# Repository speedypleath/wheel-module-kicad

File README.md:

# Haptic Console - Wheel Module (M3) Encoder Sensor Board

KiCad project for the electronics of the Wheel Module (M3) of Haptic Console v1.0,
part of the ITPMA dissertation *Tactile I/O: Exploring physicality in MIDI controllers*.

The mechanical side of this module (200 mm DIN aluminium handwheel, PETG shaft,
6204-2RS bearings, GT2 1:1 belt drive) is documented in the Obsidian vault under
`Notes/Haptic Console - Handwheel Belt Drive Module Plan.md`. This repository covers
only the sensor board that reads the optical encoder and presents it to the console.

## What the board does

The handwheel drives an E38S6G5-600B-G24N 600 P/R optical encoder through a 1:1 GT2
belt. A Raspberry Pi Pico reads the A/B quadrature signals locally, converts them into a clean position
packet, and exposes that packet to the Teensy 4.1 master over I2C. The module behaves
as a self-contained tactile sense organ rather than a peer processor, matching the
connector standard's design philosophy.

*The module as actually built. Component side, left to right: `J2` (black 5-pin encoder
header) and the pull-up/series resistors bottom left, `C2` (yellow disc) beside them,
`U1` centre with `C1`'s electrolytic can at its USB end, `J1` (white XH2.54 to the hub)
top right, and the `D1`/`D2` status LEDs bottom right.*

## The encoder interface, and why the pull-ups are there

The encoder is an **E38S6G5-600B-G24N**: photoelectric incremental, 600 P/R, rated
**DC 5-24V**, with **NPN open-collector** outputs. The `600B` suffix denotes **AB
two-phase — there is no Z index channel**. Absolute zero is established in firmware,
not from hardware index.

The open-collector output is the important electrical detail. An open-collector output can
only pull its line *low*. It never drives a line high. The high level is therefore set
entirely by whatever rail the line is pulled up to, and is completely independent of
the encoder's own supply voltage.

That gives the safety property this board relies on:

- `R1`, `R2` (4.7k) pull `ENC_A_RAW` and `ENC_B_RAW` up to **+3V3**.
- The Pico therefore sees a 0V to 3.3V swing regardless of whether the encoder is run
  from 5V or 12V.
- `R4`, `R5` (330R) sit in series into the Pico GPIO as fault-current limiters,
  protecting the pin if a line is ever accidentally shorted to the encoder supply.

4.7k is comfortable here. With ~2 m of encoder cable at roughly 120 pF/m plus pin and
stray capacitance (~300 pF total), the RC rise time is about 3 us 10-90%. At a realistic
handwheel speed of 300 rev/min each channel runs at 3 kHz, a 333 us period, so the rise
occupies under 1% of it. Pull-up current is 0.7 mA per line, far inside the output
stage's sink capability.

Without the pull-ups the inputs would float and the quadrature decode would be noise.
The pull-ups are not optional here.

Encoder power is taken from the console's **5V rail**, which is inside the encoder's
rated 5-24V window. If the encoder proves sluggish or noisy at 5V, the documented
alternative is a small 5V to 12V boost feeding `J2` pin 1 only. Because the pull-ups
reference 3.3V, that change requires **no** modification to the logic side.

**Decision, 2026-08-28: the 12V path is deliberately not built.** The planned Eurorack
translation module needs 24V regardless, so if a higher-voltage rail is ever added it
should be designed once for both modules rather than bolted onto M3 alone. Treat 5V as
the committed supply until that point. Note also that if the encoder signals ever look
sluggish, supply voltage is the *less* likely cause: edge shape here is set by the
pull-up RC (4.7k against ~300 pF, ~3 us) which does not change with encoder supply at
all. Rounded edges point at the pull-ups (fit 2.2k or 1k); missed counts that worsen
with rotation speed point at the supply.

## Console interface

`J1` is the standard **XH2.54 6-pin** inter-module connector (standard v1.1):

| Pin | Signal | Board use |
|---|---|---|
| 1 | GND | Common ground |
| 2 | 3.3V | **Not connected** (see below) |
| 3 | 5V | Powers the Pico via VSYS, and the encoder |
| 4 | SIG1 / SDA | I2C data, Pico GP4 |
| 5 | SIG2 / SCL | I2C clock, Pico GP5 |
| 6 | SIG3 / IRQ | Data-ready, Pico GP6 |

Pin 2 is deliberately left unconnected. The connector standard warns against feeding
both VSYS and 3V3 as competing power paths into a Pico. The board takes 5V into VSYS
and uses the Pico's own regulated 3V3 output as the logic reference for the pull-ups.

I2C bus pull-ups live on the master/hub board, not here, per the same standard.

## Encoder connector

`J2` is a 5-pin 2.54mm header matching the encoder's four conductors plus its shield:

| Pin | Encoder wire | Board use |
|---|---|---|
| 1 | Red | V+, from the console 5V rail |
| 2 | Black | 0V / GND |
| 3 | White | Channel A, to `R1`/`R4` |
| 4 | Green | Channel B, to `R2`/`R5` |
| 5 | Bare / foil | Cable shield, to GND |

Pin 5 carried `ENC_Z` in the first revision. The encoder has no Z channel, so it is now
the shield return, terminated to GND **at the board end only** — single-point, to avoid
a ground loop down the 2 m cable run.

## Pin map

| Pico pin | Net | Function |
|---|---|---|
| GP2 (pin 4) | LNK | Link/comms status LED |
| GP4 (pin 6) | SDA | I2C target data |
| GP5 (pin 7) | SCL | I2C target clock |
| GP6 (pin 9) | IRQ | Data-ready out to master |
| GP16 (pin 21) | ENC_A | Encoder channel A |
| GP17 (pin 22) | ENC_B | Encoder channel B |
| VSYS (pin 39) | +5V | Module power in |
| 3V3 (pin 36) | +3V3 | Logic reference out |

At 600 P/R with 4x quadrature decoding, one full handwheel turn is 2400 counts.

## Why C1 is there, and why it is an electrolytic

C1 is a **bulk reservoir**, not a decoupling capacitor, and the two jobs are
different. C2 (100 nF on 3V3) is decoupling: it kills the nanosecond-scale current
spikes from GPIO switching, and wants to be small and close to the pin. C1 sits on
the 5 V rail at the connector entry and does the opposite job — it is a local charge
store at the far end of the hub cable.

The 5 V arrives over a metre or two of XH2.54 flying lead, perhaps 1 uH/m of
inductance plus some milliohms. Every change in this board's load current has to be
supplied through that inductance: the encoder's output transistors switching at
2 x 3 kHz, the Pico's RT6150 buck-boost drawing pulsed input current, and above all
**hot-plugging J2 with the encoder attached**. Without local bulk the rail at VSYS
dips and rings instead of holding up. Steady-state draw is modest — encoder
40-100 mA, Pico 25-30 mA, LEDs ~3 mA — so it is the transients that matter.

100 nF will not do this job: it is 100x less charge. A 100 mA step lasting 300 ns
gives dV = I*dt/C ~= 300 mV on 100 nF against ~3 mV on 10 uF, and it moves the
cable-inductance resonance from ~50 kHz up to ~500 kHz where it is far less damped.

**Electrolytic is the right part, not a compromise** — bulk capacitance is what
aluminium electrolytics are for. The first revision specified a 10 uF ceramic only
because `Device:CP` cached as a zero-pin stub during project creation and switching
to the non-polarised `Device:C` sidestepped the question. (The real cause was
simpler: KiCad 10 has no `Device:CP` at all; the symbol is `Device:C_Polarized`.)

**C1 is now polarised, and nothing in ERC or DRC will catch it if you fit it
backwards.** Pad 1 is **+** and goes to `+5V`; the lead beside the printed stripe is
**-** and goes to `GND`. On a 5 V rail a reversed electrolytic will vent. Both build
guides call this out at the step where it matters.

## Bill of materials

| Ref | Value | Footprint |
|---|---|---|
| U1 | Raspberry Pi Pico | Module:RaspberryPi_Pico_Common_THT |
| J1 | XH2.54 6-pin console connector | Connector_JST:JST_XH_B6B-XH-A_1x06_P2.50mm_Vertical |
| J2 | 5-pin encoder header | Connector_PinHeader_2.54mm:PinHeader_1x05_P2.54mm_Vertical |
| R1, R2 | 4.7k pull-up to 3.3V | Resistor_THT:R_Axial_DIN0207_L6.3mm_D2.5mm_P10.16mm_Horizontal |
| R4, R5 | 330R series protection | Resistor_THT:R_Axial_DIN0207_L6.3mm_D2.5mm_P10.16mm_Horizontal |
| R7, R8 | 1k LED current limit | Resistor_THT:R_Axial_DIN0207_L6.3mm_D2.5mm_P10.16mm_Horizontal |
| C1 | 10uF 25V bulk on 5V, **polarised** | wheel-module:CP_Radial_D4.0mm_P2.50mm |
| C2 | 100nF decoupling on 3.3V | Capacitor_THT:C_Disc_D5.0mm_W2.5mm_P5.00mm |
| D1 | PWR green 3mm | LED_THT:LED_D3.0mm |
| D2 | LNK red 3mm | LED_THT:LED_D3.0mm |

D1 and D2 match the PWR/LNK status cluster in the front panel drawing
(`Notes/Haptic Console - Wheel Module Front Panel.md`).

## Layouts and build guides

One schematic, three board files. They share the netlist and nothing else — pick the one
that matches how you are building.

| Build | Board file | Build guide |
|---|---|---|
| Stripboard (Veroboard) | `project/haptic-console-wheel-module-stripboard.kicad_pcb` | [`docs/stripboard-wiring.md`](docs/stripboard-wiring.md), or the interactive [`docs/stripboard-wiring.html`](docs/stripboard-wiring.html) with a live board map |
| Plain perfboard | `project/haptic-console-wheel-module-perfboard.kicad_pcb` | [`docs/perfboard-wiring.md`](docs/perfboard-wiring.md) |
| Fabricated PCB | `project/haptic-console-wheel-module.kicad_pcb` | none needed — [Gerber set](project/haptic-console-wheel-module-gerbers.zip) |

### Schematic

Full page as [`renders/schematic-v2.pdf`](renders/schematic-v2.pdf). ERC report:
[`docs/erc-report.txt`](docs/erc-report.txt); exported netlist:
[`docs/netlist.net`](docs/netlist.net).

### Stripboard (Veroboard)

40 x 40 holes, 104.14 mm square — the full uncut board. The circuit lives in cols 1-28 /
rows 1-28; the strips run the board's whole width regardless, which is why the audit
matters more than the placement.

| Component side | Solder side |
|---|---|
|  |  |

The solder-side view is the one to build from: white `X` marks are the 23 track cuts, and
the coloured rods are the eight link wires, drawn to the control unit's colour convention
(red power, blue GND, yellow I2C/IRQ, green `/LNK`). Cuts and links are listed
step-by-step in [`docs/stripboard-wiring.md`](docs/stripboard-wiring.md).

### Plain perfboard

28 x 28 holes, 71.12 mm square, every connection a discrete wire.

Wire-by-wire build order in [`docs/perfboard-wiring.md`](docs/perfboard-wiring.md).

### Fabricated PCB

68 x 58 mm, 2-layer, all through-hole.

| Front (F.Cu) | Back (B.Cu) |
|---|---|
|  |  |

The back is mostly the filled GND pour that all 14 GND pads tie into; only `/LNK` and the
`+3V3` branch to `R7` are routed there.

## Status

- Schematic: complete, **ERC 0 errors / 0 warnings**, netlist verified by parsing the
  exported `docs/netlist.net` — 13 components, 15 nets, every node checked against the
  pin map above. A clean ERC alone does not prove connectivity; always read the netlist.
- Encoder revision: `ENC_Z`, `R3` and `R6` removed after the datasheet confirmed the
  `600B` part is AB two-phase. `J2` pin 5 repurposed as shield. GP18 is now free.
- Perfboard layout: **complete**, 28x28 holes on 2.54mm pitch (71.12 x 71.12 mm cut),
  **0 DRC errors / 9 cosmetic warnings**. Every pad verified on-grid with no shared
  holes. The 32 unconnected pads DRC reports are expected -
  the board is hand-wired and carries no copper traces.
- Stripboard (Veroboard) layout: **complete**, 40x40 holes on 2.54mm pitch
  (104.14 mm square, the full uncut board), **0 DRC errors / 0 unconnected pads**.
  The circuit occupies cols 1-28 / rows 1-28; the rest is spare board, but the
  strips still run its full width. Continuous copper
  strips, 23 track cuts, 11 link connections. Two cuts are
  load-bearing: row 9 keeps **AGND** off the GND bus, and column 5 keeps `J1` pin 2
  (hub 3.3V) unconnected. Rows 4/14/19 are left uncut on purpose - they carry GND on
  both sides of the Pico and form the GND bus for free. The ~240 DRC warnings are
  expected: perfboard holes modelled as vias dangle by construction.
  Generated from `scripts/layout.py` by the shared `~/KiCad/kicad-stripboard`
  engine - rebuild it rather than editing the board.
  The eight physical link wires are modelled as colour-coded 3D jumper wires on the
  **solder** side, keeping the crowded component side clear.
- Manufactured PCB layout: **complete**, 2-layer, 68 x 58 mm, all through-hole.
  **0 DRC errors, 0 shorts, 0 unconnected items** — every net is connected. 38 routed
  segments plus a filled GND pour on `B.Cu` (3270 mm² of copper), which all 14 GND pads
  tie into directly, so GND needs no traces. Two runs sit on the back layer because they would otherwise cross the J1 signal fan
  on the front: `/LNK` (U1.4 → R8.1) and the `+3V3` branch feeding R7, which goes round
  the bottom at y=56.5 rather than threading the 0.94 mm gaps between the Pico's pad
  rows. The front `+3V3` spine is offset to x=48.5 rather than running down the x=46.5
  pad column, because R5.1 (`/ENC_B`) sits mid-column at 46.5,43.18.
- Cosmetic: reference and value text is auto-placed and overlaps net labels in a few
  places. Harmless electrically, but worth a tidy-up pass in the GUI before the
  schematic goes into the dissertation.

## Verification

```bash
export KICAD_SYMBOL_DIR=/Applications/KiCad/KiCad.app/Contents/SharedSupport/symbols
export KICAD_FOOTPRINT_DIR=/Applications/KiCad/KiCad.app/Contents/SharedSupport/footprints
kicad-cli sch erc --format report project/haptic-console-wheel-module.kicad_sch -o docs/erc-report.txt
kicad-cli sch export netlist --format kicadsexpr project/haptic-console-wheel-module.kicad_sch -o docs/netlist.net
```

Setting both environment variables matters. Without them `kicad-cli` cannot resolve the
stock libraries and reports spurious violations.

## Related

- [`docs/perfboard-wiring.md`](docs/perfboard-wiring.md) - hand-wiring guide for the
  plain-perfboard build
- [`docs/stripboard-wiring.md`](docs/stripboard-wiring.md) - cut/link build guide for the
  Veroboard build, plus the interactive
  [`docs/stripboard-wiring.html`](docs/stripboard-wiring.html)
- [`scripts/layout.py`](scripts/layout.py) - the stripboard layout as data; source of
  truth for that board
- `../kicad-stripboard` - the shared engine that builds and audits strip board layouts
- `../control-unit-kicad` - the Control Unit (M6) board, already fab-ready
- Obsidian: `Notes/Haptic Console - Connector Standard.md`
- Obsidian: `concepts/haptic-console-wheel-module.md`

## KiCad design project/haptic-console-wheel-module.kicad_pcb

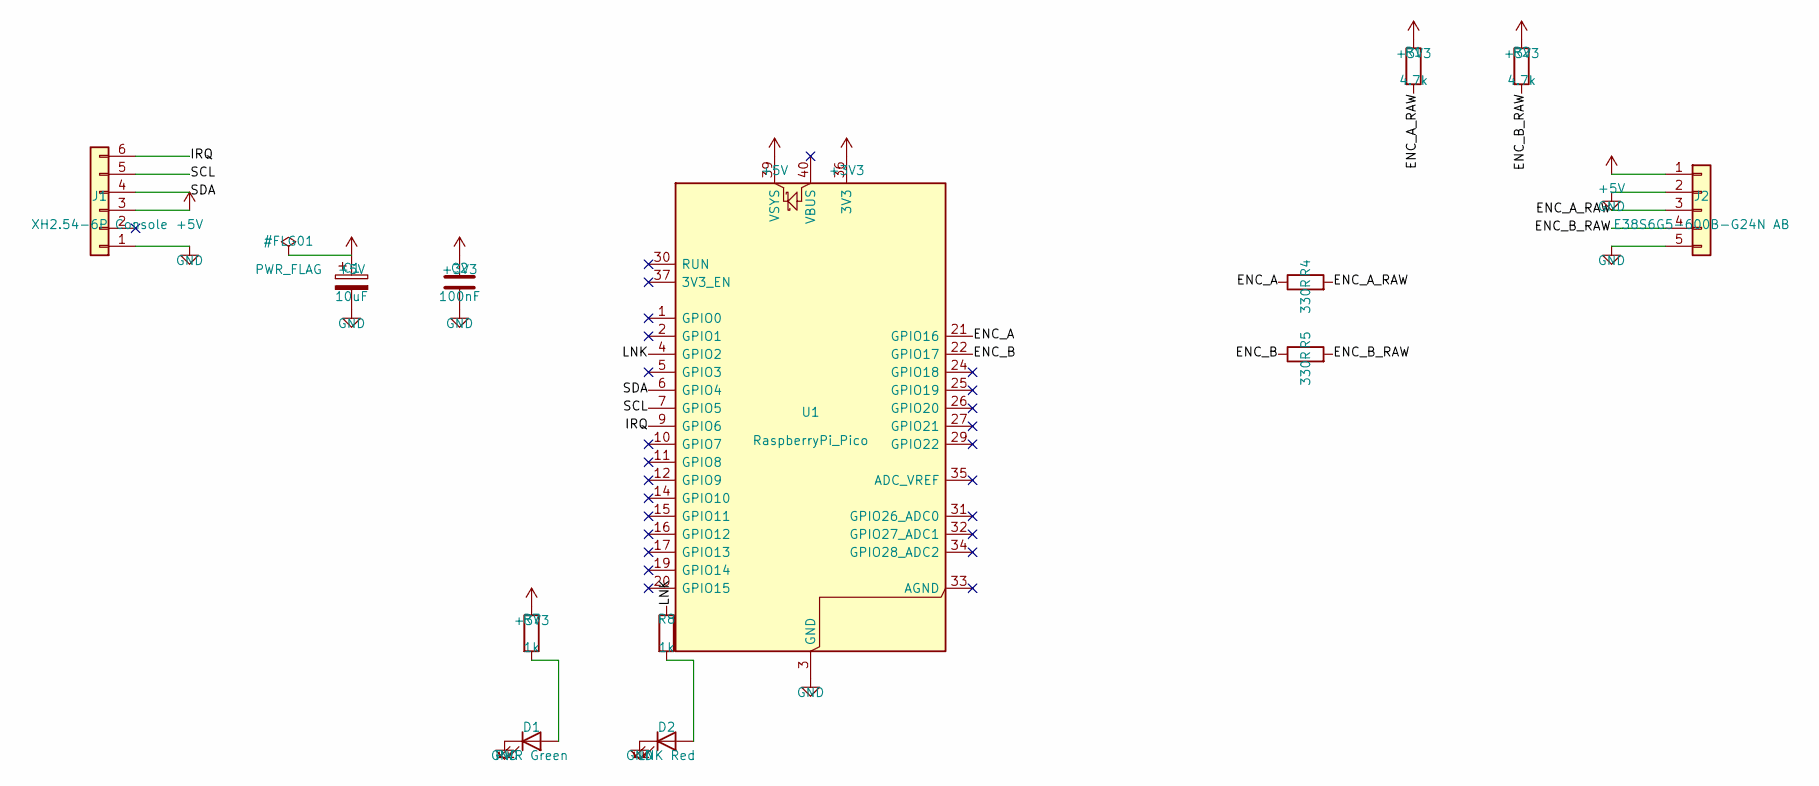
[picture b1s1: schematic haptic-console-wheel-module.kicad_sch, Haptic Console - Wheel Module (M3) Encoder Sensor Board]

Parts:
C1: 10uF; CP_Radial_D4.0mm_P2.50mm; Voltage 25V
C2: 100nF; C_Disc_D5.0mm_W2.5mm_P5.00mm
D1: PWR Green; LED_D3.0mm
D2: LNK Red; LED_D3.0mm
J1: XH2.54-6P Console; JST_XH_B6B-XH-A_1x06_P2.50mm_Vertical
J2: E38S6G5-600B-G24N AB; PinHeader_1x05_P2.54mm_Vertical
R1, R2: 4.7k; R_Axial_DIN0207_L6.3mm_D2.5mm_P10.16mm_Horizontal
R4, R5: 330R; R_Axial_DIN0207_L6.3mm_D2.5mm_P10.16mm_Horizontal
R7, R8: 1k; R_Axial_DIN0207_L6.3mm_D2.5mm_P10.16mm_Horizontal
U1: RaspberryPi_Pico; RaspberryPi_Pico_Common_THT

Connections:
+3V3: C2.1, R1.1, R2.1, R7.1, U1.36 (3V3)
+5V: C1.1, J1.3, J2.1, U1.39 (VSYS)
/ENC_A: R4.1, U1.21 (GPIO16)
/ENC_A_RAW: J2.3, R1.2, R4.2
/ENC_B: R5.1, U1.22 (GPIO17)
/ENC_B_RAW: J2.4, R2.2, R5.2
/IRQ: J1.6, U1.9 (GPIO6)
/LNK: R8.1, U1.4 (GPIO2)
/SCL: J1.5, U1.7 (GPIO5)
/SDA: J1.4, U1.6 (GPIO4)
GND: C1.2, C2.2, D1.1 (K), D2.1 (K), J1.1, J2.2, J2.5, U1.3 (GND), U1.8 (GND), U1.13 (GND), U1.18 (GND), U1.23 (GND), U1.28 (GND), U1.38 (GND)
unnamed: D1.2 (A), R7.2
unnamed: D2.2 (A), R8.2

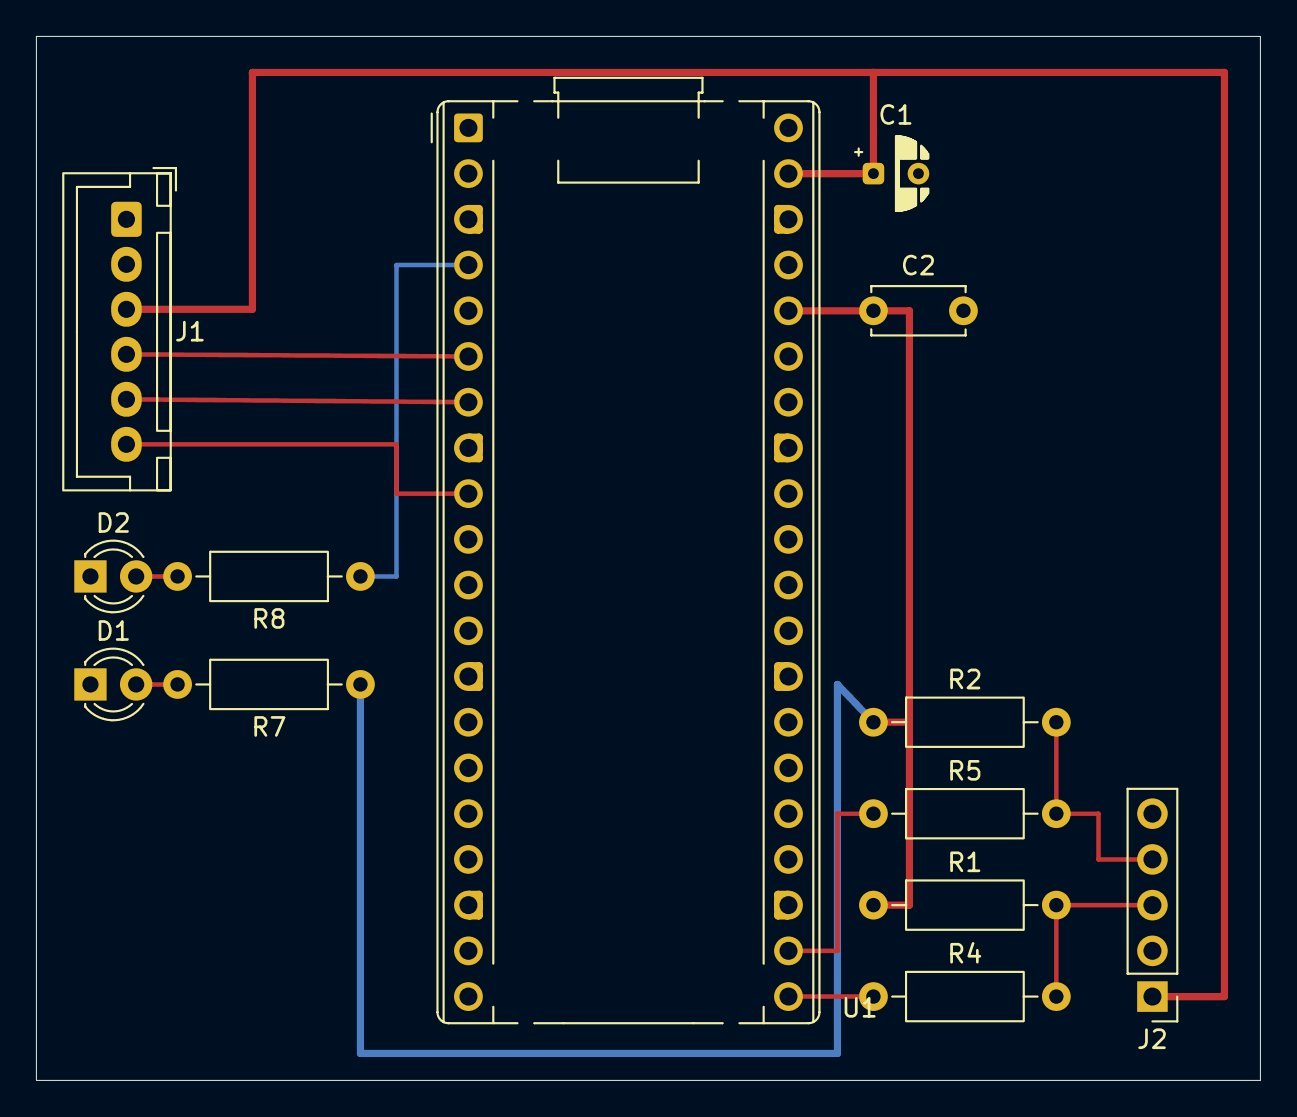
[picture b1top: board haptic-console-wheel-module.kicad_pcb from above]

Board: 2 copper layers, 68.0 x 58.0 mm, 13 parts (0 on the bottom side), 13 nets.
